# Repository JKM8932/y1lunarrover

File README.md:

# y1lunarrover

This serves as a repository for Group 29 of the 1stYear 2026, dedicated to the Lunar Rover project. Project ideas, preliminary circuit diagrams and software programmes will be documented here.

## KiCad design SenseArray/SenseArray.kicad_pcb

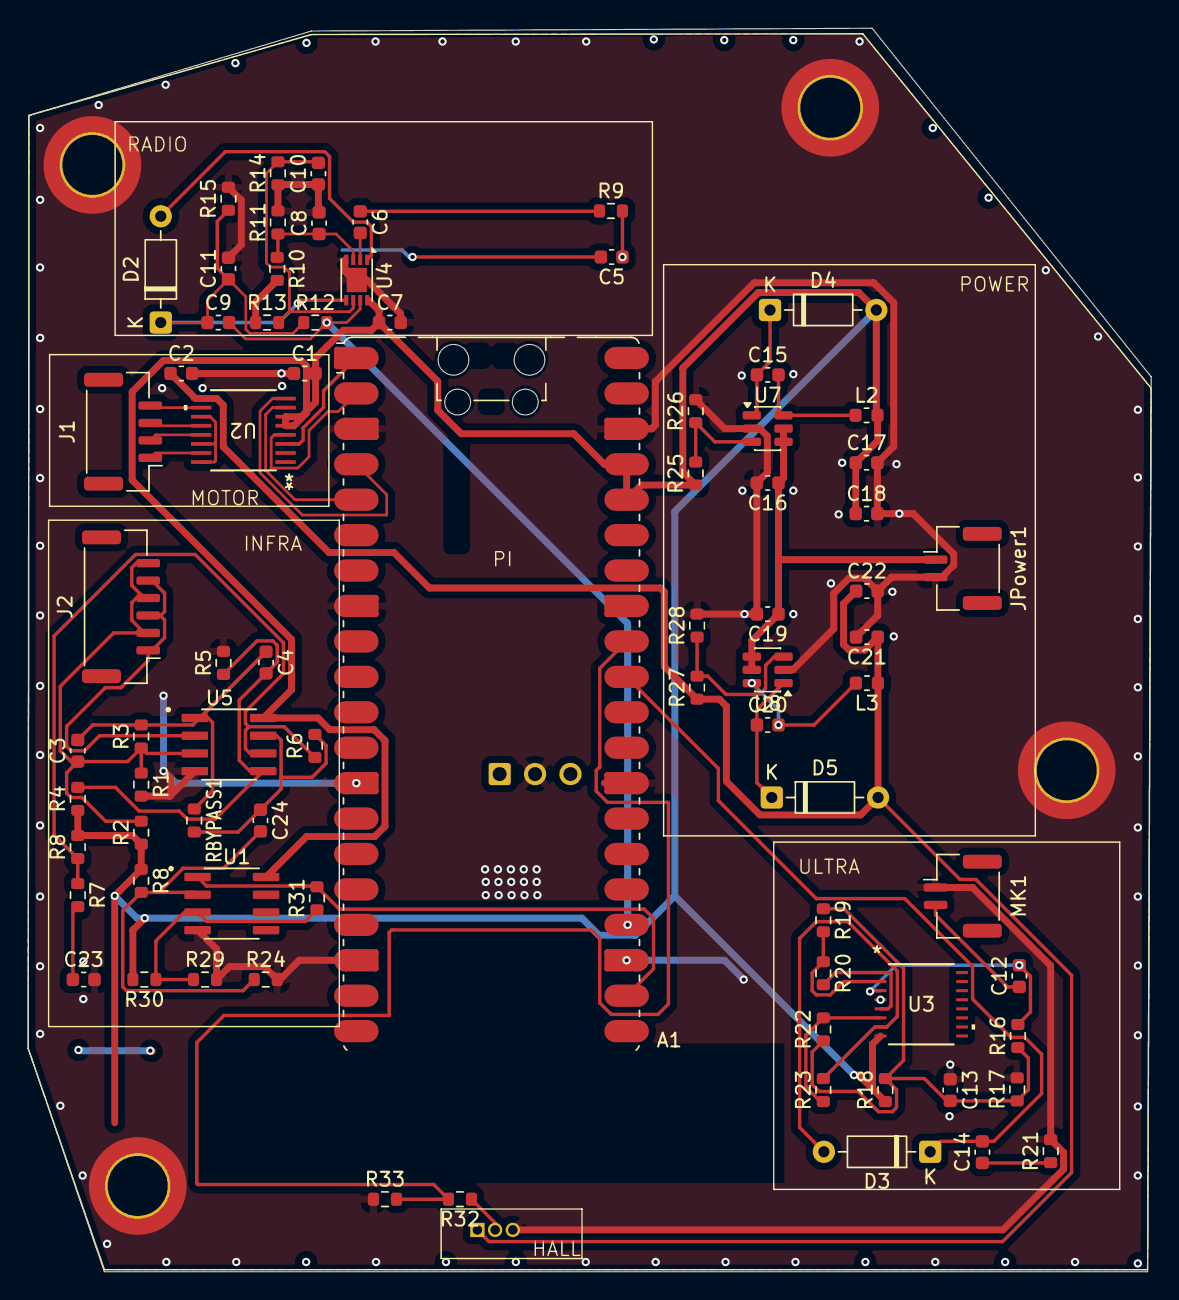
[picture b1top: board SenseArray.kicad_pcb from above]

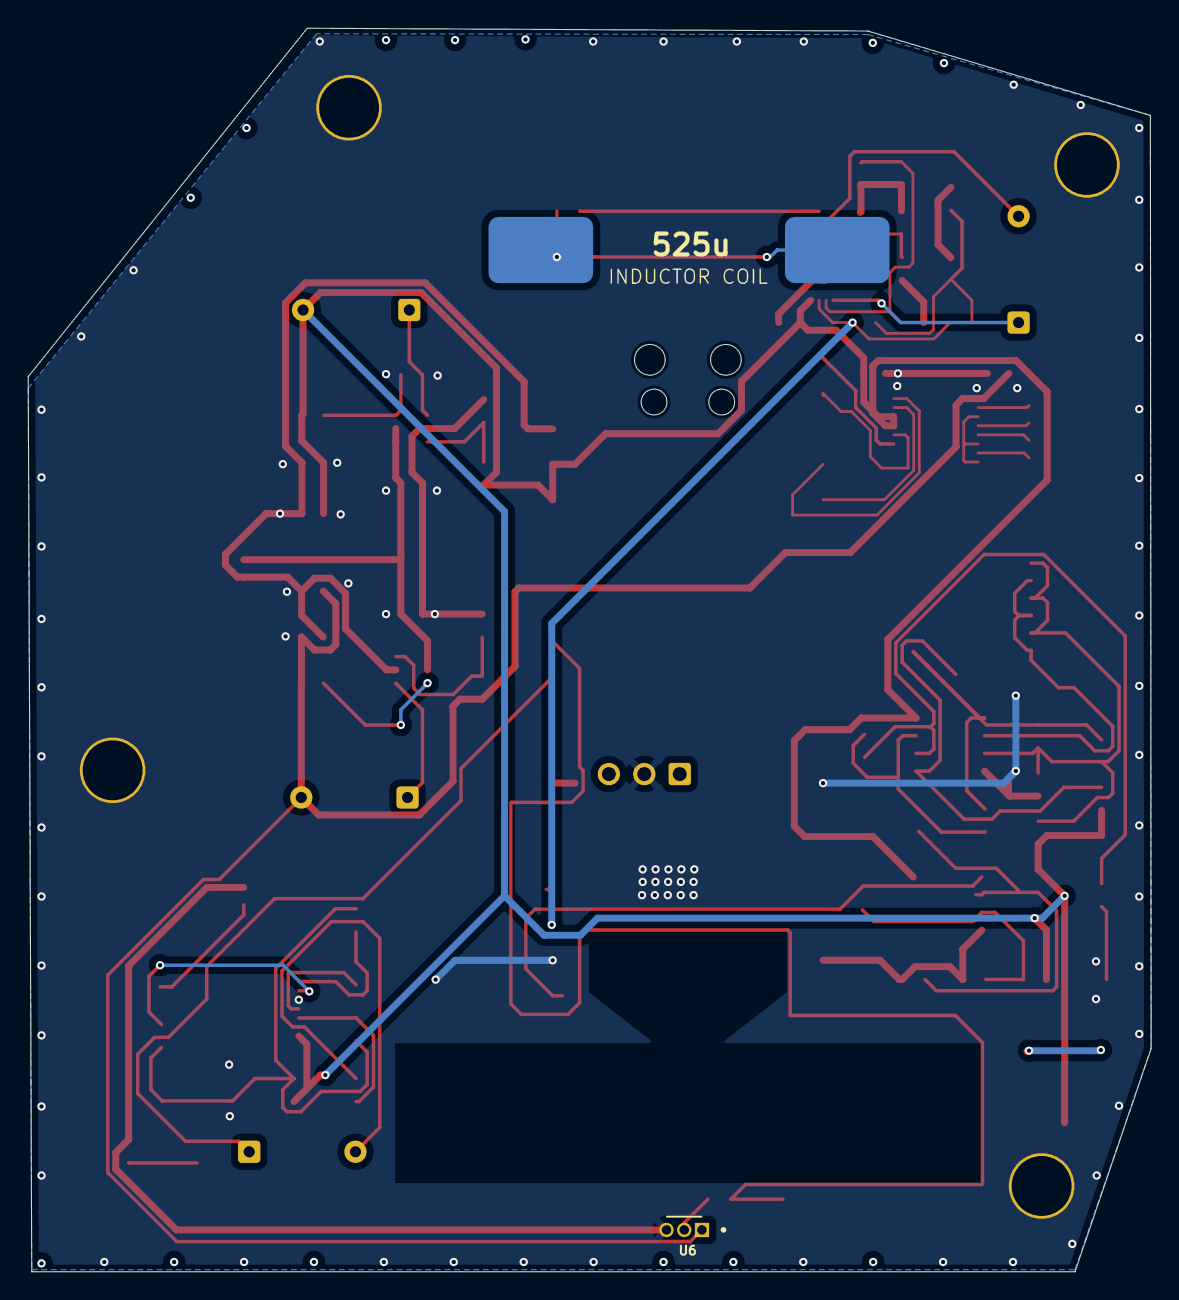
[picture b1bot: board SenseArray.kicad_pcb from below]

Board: 2 copper layers, 80.5 x 89.1 mm, 83 parts (2 on the bottom side), 48 nets.

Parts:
A1: RaspberryPi_Pico_W; RaspberryPi_Pico_W_SMD_HandSolder
C1, C2, C7, C8, C10, C13, C15, C20: 100n; C_0603_1608Metric
C3, C9: 22p; C_0603_1608Metric
C4, C6, C23, C24: 1u; C_0603_1608Metric
C5: 6.2n; C_0603_1608Metric
C11: 2.2n; C_0603_1608Metric
C12, C14: 10n; C_0603_1608Metric
C16, C17, C18, C19, C21, C22: 10u; C_0603_1608Metric
D2, D3, D4, D5: 1N4148; D_DO-35_SOD27_P7.62mm_Horizontal
J1: Conn_01x04_Pin; JST_GH_BM04B-GHS-TBT_1x04-1MP_P1.25mm_Vertical
J2: Conn_01x06_Pin; JST_GH_BM06B-GHS-TBT_1x06-1MP_P1.25mm_Vertical
J3, J4, J5, J6: Conn_01x01_Pin; MountingHole_4.3mm_M4_ISO14580_Pad_TopOnly
JPower1: Conn_01x02_Pin; JST_GH_BM02B-GHS-TBT_1x02-1MP_P1.25mm_Vertical
L1: 517u; Untitled
L2: 15u; L_0603_1608Metric
L3: 20u; L_0603_1608Metric
MK1: Microphone_Ultrasound; JST_GH_BM02B-GHS-TBT_1x02-1MP_P1.25mm_Vertical
R1, R2, R4, R5, R8#2, R9, R15, R17, R18, R24, R26, R28, R29, R32, R33: 10k; R_0603_1608Metric
R3: 180k; R_0603_1608Metric
R6: 68k; R_0603_1608Metric
R7: 39k; R_0603_1608Metric
R8, R14, R30: 15k; R_0603_1608Metric
R10, R11, R12, R16: 100k; R_0603_1608Metric
R13: 27k; R_0603_1608Metric
R19, R22, R23: 1k; R_0603_1608Metric
R20: 9k; R_0603_1608Metric
R21: 47k; R_0603_1608Metric
R25: 31.6k; R_0603_1608Metric
R27: 65k; R_0603_1608Metric
R31: 200k; R_0603_1608Metric
RBYPASS1: NA; R_0603_1608Metric
U1, U5: MCP6292-E_SN; SOIC127P600X175-8N
U2: TC78H620FNG_EL; SSOP16-P-225-0p65B_TOS-M
U3: MCP6292-E_SN; SSOP16-P-225-0p65B_TOS-L
U4: MCP6002-xMC; DFN-8-1EP_3x2mm_P0.5mm_EP1.75x1.45mm
U6: A1102xLH; XDCR_SS495A
U7, U8: MCP16301Hx-xCH; SOT-23-6

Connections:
/3v3: A1.36 (3V3), A1.37 (3V3_EN), C1.2, C7.1, C17.1, C18.1, D4.2 (A), L2.2, R2.1, R4.1, R8.2, R8#2.1, R10.2, R13.1, R18.1, R25.1, R30.2, U1.8 (VDD), U2.5 (VCC), U2.6 (/STBY), U3.8 (VDD), U4.8 (V+), U5.8 (VDD)
/6v: C2.1, C21.1, C22.1, D5.2 (A), L3.1, R27.1, U2.9 (VM), U6.1 (V_{CC})
/BYPASS: C3.2, C4.1, R3.2, RBYPASS1.1, U5.1 (VOUTA)
/EN_LEFT: A1.1 (GPIO0), U2.3 (PHA_A)
/EN_RIGHT: A1.4 (GPIO2), U2.8 (EN_B)
/IR_1_OUT: C4.2, R4.2, R5.1, U5.5 (VINB+)
/IR_2_OUT: C24.1, R6.2, RBYPASS1.2, U5.7 (VOUTB)
/IR_3_IN: C24.2, R8#2.2, R24.1, U1.2 (VINA-)
/IR_G: C3.1, J2.2, J2.4, J2.6, R1.1, R2.2, R3.1, U5.3 (VINA+)
/IR_I: J2.1, J2.3, J2.5, U5.2 (VINA-)
/IR_OUT: A1.22 (GPIO17), R31.2, U1.1 (VOUTA)
/MAGNET_OUT: A1.32 (GPIO27_ADC1), R32.2, R33.2
/PH_LEFT: A1.2 (GPIO1), U2.4 (EN_A)
/PH_RIGHT: A1.5 (GPIO3), U2.7 (PHA_B)
/RADIO_OUT: A1.24 (GPIO18), C9.2, R12.2, U4.7
/ULTRA_OUT: A1.31 (GPIO26_ADC0), C14.2, D3.1 (K)
/V1_Out: R20.2, U3.1 (VOUTA), U3.5 (VINB+)
/V2_Out: D3.2 (A), R23.2, U3.7 (VOUTB)
/VINA+: C12.2, R16.2, U3.3 (VINA+)
/VINB-: R6.1, R7.1, R8.1, U5.6 (VINB-)
GND: A1.3 (GND), A1.8 (GND), A1.13 (GND), A1.18 (GND), A1.23 (GND), A1.28 (GND), A1.38 (GND), A1.D2 (GND), C1.1, C2.2, C7.2, C8.2, C10.1, C11.2, C13.1, C16.2, C17.2, C18.2, C19.2, C21.2, C22.2, C23.2, J3.1, J4.1, J5.1, J6.1, JPower1.2, MK1.1 (-), R1.2, R5.2, R11.2, R14.1, R15.2, R17.2, R21.2, R24.2, R26.2, R28.2, R29.2, R33.1, U1.4 (VSS), U3.4 (VSS), U4.4 (V-), U4.9 (V-), U5.4 (VSS), U6.3 (GND), U7.2 (GND), U8.2 (GND)
unnamed: C5.1, R9.2
unnamed: C6.1, R9.1
unnamed: C13.2, R16.1, R17.1, R18.2, R19.1, R22.1
unnamed: C14.1, R21.1
unnamed: C23.1, R7.2
unnamed: D2.2 (A), U4.1
unnamed: C9.1, C11.1, D2.1 (K), R12.1, R15.1, U4.5 (+)
unnamed: C15.1, D4.1 (K), U7.1 (BOOST)
unnamed: C20.1, D5.1 (K), U8.1 (BOOST)
unnamed: J1.1, U2.15 (AO1)
unnamed: J1.2, U2.13 (AO2)
unnamed: J1.3, U2.12 (BO1)
unnamed: J1.4, U2.10 (BO2)
unnamed: C16.1, C19.1, JPower1.1, U7.4 (EN), U7.5 (V_{IN}), U8.4 (EN), U8.5 (V_{IN})
unnamed: C12.1, MK1.2 (+)
unnamed: R29.1, R30.1, R31.1, U1.3 (VINA+)
unnamed: U2.11 (GND), U2.14 (GND), U2.16 (GND)
unnamed: R19.2, R20.1, U3.2 (VINA-)
unnamed: R22.2, R23.1, U3.6 (VINB-)
unnamed: C8.1, R10.1, R11.1, U4.3 (+)
unnamed: C6.2, U4.2 (-)
unnamed: C10.2, R13.2, R14.2, U4.6 (-)
unnamed: R32.1, U6.2 (V_{OUT})
unnamed: C15.2, L2.1, U7.6 (SW)
unnamed: R25.2, R26.1, U7.3 (Vfb)
unnamed: C20.2, L3.2, U8.6 (SW)
unnamed: R27.2, R28.1, U8.3 (Vfb)

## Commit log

2026-05-19 Create Infrared
2026-05-19 Create Notes
2026-05-19 Create initialtestcode
2026-05-19 Rename Notes to Notes.md
2026-05-26 Rename Receiver&AmplifierLTSPICE.md to Receiver&AmplifierLTSPICE(old).md
2026-05-26 Rename FullAgeDetectorLTSPICE.md to FullAgeDetectorLTSPICE.png
2026-06-01 Implement ADC reading and direction detection
    This program reads ADC values from a sensor, applies a moving average filter to smooth out readings, and determines the direction based on deviations from a calibrated baseline.
2026-06-04 Refactor ADC handling and calibration logic
    Updated ADC filter size and threshold values for improved sensitivity. Refactored smoothing function and calibration process for better performance.
2026-06-05 Add motor control implementation with UDP support
2026-06-07 Rename image.png to PCBDesign/entirepcb.png
2026-06-07 Rename entirepcb.png to fullpcb.png
2026-06-07 Rename image.png to PCBDesign/infraredpcb.png
2026-06-07 Rename image.png to PCBDesign/powerforpcb.png
2026-06-07 Rename image.png to radiopcb/image.png
2026-06-07 Rename image.png to radiopcb.png
2026-06-07 Rename image.png to PCBDesign/ultrasoundpcb.png
2026-06-07 Rename image.png to PCBDesign/motordrivepcb.png
2026-06-07 Rename Screenshot 2026-06-07 at 22-39-06 Inbox - Mak Justin K - Outlook.png to PCBDesign/magneticpcb.png
2026-06-07 Rename image.png to PCBDesign/picolayoutpcb.png
2026-06-08 Add motor control test for Pico W
2026-06-08 Rename motor_control.cpp to chassis/drive/motor_control.cpp
2026-06-08 Rename motor_control.cpp to motor_control.c
2026-06-08 Update motor pin definitions
2026-06-09 Created updated_motor_control.c
    Rewrote code so that it can be integrated into the main programme, and added gears to change the speed.
2026-06-10 Add motor control testing file
2026-06-10 Software
2026-06-10 Final_Circuit_Schematic
2026-06-11 Move motor_control_testing.c to Chassis directory
2026-06-11 Move motor_control_testing.c to Drive directory
2026-06-11 Rename Chassis/Drive/motor_test.c to Drive/motor_test.c
2026-06-11 Rename Chassis/Drive/updated_motor_control.c to Drive/updated_motor_control.c
2026-06-11 Rename Screenshot 2026-06-11 at 1.12.34 PM.jpg to Infrared/FullCircuit(TIA)+OptionalStage(RED).jpg
2026-06-11 Rename Screenshot 2026-06-11 at 1.22.11 PM.jpg to Infrared/FullCircuit(LoadAmplifier).jpg
2026-06-11 Rename Screenshot 2026-06-11 at 1.25.02 PM.jpg to Magnetic/FullCircuit(Diffamplifier).jpg
2026-06-11 Rename Screenshot 2026-06-11 at 13-31-39 Optional amplifier stage that can be bypassed when not needed - Presentation.png to PCBDesign/infraredpcb.png
2026-06-11 Rename Screenshot 2026-06-11 at 13-53-45 Optional amplifier stage that can be bypassed when not needed - Presentation.png to PCBDesign/radiopcb.png
2026-06-11 Rename Screenshot 2026-06-11 at 13-54-02 Optional amplifier stage that can be bypassed when not needed - Presentation.png to PCBDesign/ultrasoundpcb.png
2026-06-12 Rename motor.c to Motor.c
2026-06-12 Rename motor.h to Motor.h
2026-06-12 Rename radio.c to Radio.c
2026-06-12 Rename radio.h to Radio.h
2026-06-12 Rename Screenshot 2026-06-12 at 11-32-43 Inbox - Mak Justin K - Outlook.png to Infrared/FinalCircuitIR.png
2026-06-12 Rename WhatsApp Video 2026-06-12 at 11.46.11.mp4 to Ultrasound/demovideo.mp4
2026-06-12 Rename WhatsApp Video 2026-06-12 at 11.46.11(1).mp4 to Ultrasound/demovideo.mp4
2026-06-12 Rename Screenshot 2026-06-12 at 6.26.37 PM.jpg to Magnetic/finalschematic.jpg
2026-06-15 Rename Screenshot 2026-06-15 at 12.26.03 PM.jpg to Magnetic/finalschematic.jpg
2026-06-15 Demo Video
2026-06-15 Final Schematic
